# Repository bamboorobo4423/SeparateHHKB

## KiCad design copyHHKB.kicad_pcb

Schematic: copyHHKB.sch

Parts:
!1: SW_DIP_x01; MX_PCB_100H
$1: SW_DIP_x01; MX_PCB_100H
%1: SW_DIP_x01; MX_PCB_100H
&1: SW_DIP_x01; MX_PCB_100H
'1: SW_DIP_x01; MX_PCB_100H
(1: SW_DIP_x01; MX_PCB_100H
)1: SW_DIP_x01; MX_PCB_100H
*1: SW_DIP_x01; MX_PCB_100H
+1: SW_DIP_x01; MX_PCB_100H
/1: SW_DIP_x01; MX_PCB_100H
;1: SW_DIP_x01; MX_PCB_100H
<1: SW_DIP_x01; MX_PCB_100H
>1: SW_DIP_x01; MX_PCB_100H
@1: SW_DIP_x01; MX_PCB_100H
AltL1: SW_DIP_x01; Hybrid_Plate_125H
AltR1: SW_DIP_x01; Hybrid_Plate_125H
BackSP1: SW_DIP_x01; Hybrid_Plate_150H
Control1: SW_DIP_x01; Hybrid_Plate_175H
D1, D2, D3, D4, D5, D6, D7, D8, D9, D10, D11, D12, D13, D14, D15, D16, D17, D18, D19, D20, D21, D22, D23, D24, D25, D26, D27, D28, D29, D30, D31, D32, D33, D34, D35, D36, D37, D38, D39, D40, D41, D42, D43, D44, D45, D46, D47, D48, D49, D50, D51, D52, D53, D54, D55, D56, D57, D58, D59, D60: D; Diode-dual
D61: D; Diode
ESC1: SW_DIP_x01; Hybrid_PCB_100H
Enter1: SW_DIP_x01; Hybrid_PCB_225H
Fn1: SW_DIP_x01; Hybrid_PCB_100H
J1, J2: MJ-4PP-9; MJ-4PP-9_rev2
L1: SW_DIP_x01; Hybrid_PCB_100H
SP1: SW_DIP_x01; MX_PCB_275H
SP2: SW_DIP_x01; MX_Plate_225H
U1, U2: ProMicro
[1: SW_DIP_x01; MX_PCB_100H
]1: SW_DIP_x01; MX_PCB_100H
^1: SW_DIP_x01; MX_PCB_100H
_1: SW_DIP_x01; MX_PCB_100H
`1: SW_DIP_x01; MX_PCB_100H
a1: SW_DIP_x01; MX_PCB_100H
b1: SW_DIP_x01; MX_PCB_100H
c1: SW_DIP_x01; MX_PCB_100H
d1: SW_DIP_x01; MX_PCB_100H
e1: SW_DIP_x01; Hybrid_PCB_100H
f1: SW_DIP_x01; Hybrid_PCB_100H
g1: SW_DIP_x01; Hybrid_PCB_100H
h1: SW_DIP_x01; Hybrid_PCB_100H
i1: SW_DIP_x01; Hybrid_PCB_100H
j1: SW_DIP_x01; Hybrid_PCB_100H
k1: SW_DIP_x01; Hybrid_PCB_100H
m1: SW_DIP_x01; Hybrid_PCB_100H
n1: SW_DIP_x01; Hybrid_PCB_100H
o1: SW_DIP_x01; Hybrid_PCB_100H
p1: SW_DIP_x01; Hybrid_PCB_100H
p2, p3: 3pin; StripLED_rev
q1: SW_DIP_x01; Hybrid_PCB_100H
r1: SW_DIP_x01; Hybrid_PCB_100H
s1: SW_DIP_x01; Hybrid_PCB_100H
s2, s3: sw; TSHA-T-2.5B2-19E]
sharp1: SW_DIP_x01; MX_Plate_100H
shiftL1: SW_DIP_x01; Hybrid_Plate_225H
shiftR1: SW_DIP_x01; Hybrid_Plate_175H
t1: SW_DIP_x01; MX_Plate_100H
tab1: SW_DIP_x01; Hybrid_PCB_150H
u1: SW_DIP_x01; MX_Plate_100H
v1: SW_DIP_x01; MX_Plate_100H
w1: SW_DIP_x01; MX_Plate_100H
winL1: SW_DIP_x01; MX_Plate_100H
winR1: SW_DIP_x01; MX_Plate_100H
x1: SW_DIP_x01; MX_Plate_100H
y1: SW_DIP_x01; MX_Plate_100H
z1: SW_DIP_x01; MX_Plate_100H
|1: SW_DIP_x01; MX_Plate_100H

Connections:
LGND: J2.C, U2.3 (GND), U2.4 (GND), U2.23 (GND), p3.1 (GND), s3.1
LLED: U2.1 (TX), p3.2
LVCC: J2.D, U2.21 (VCC), p3.3 (VCC)
Lcol6: U2.20 (F4), ^1.1, h1.1, y1.1
Lcol7: &1.1, U2.19 (F5), j1.1, n1.1, u1.1
Lcol8: *1.1, SP2.1, U2.18 (F6), i1.1, k1.1, m1.1
Lcol9: (1.1, <1.1, L1.1, U2.17 (F7), `1.1, o1.1
Lcol10: )1.1, ;1.1, >1.1, U2.16 (B1), p1.1, winR1.1
Lcol11: '1.1, /1.1, AltR1.1, U2.15 (B3), [1.1, _1.1
Lcol12: +1.1, Fn1.1, U2.14 (B2), ]1.1
Lcol13: BackSP1.1, Enter1.1, U2.13 (B6), shiftR1.1, |1.1
Ldate: J2.B, U2.2 (RX)
Lrow0: D28.1 (K), D31.1 (K), D35.1 (K), D39.1 (K), D44.1 (K), D49.1 (K), D54.1 (K), D57.1 (K), U2.7 (D4)
Lrow1: D29.1 (K), D32.1 (K), D36.1 (K), D40.1 (K), D45.1 (K), D50.1 (K), D55.1 (K), D58.1 (K), U2.8 (C6)
Lrow2: D30.1 (K), D33.1 (K), D37.1 (K), D41.1 (K), D46.1 (K), D51.1 (K), D59.1 (K), U2.9 (D7)
Lrow3: D34.1 (K), D38.1 (K), D42.1 (K), D47.1 (K), D52.1 (K), D56.1 (K), D60.1 (K), U2.10 (E6)
Lrow4: D43.1 (K), D48.1 (K), D53.1 (K), D61.1 (K), U2.11 (B4)
unnamed: !1.2, D5.2 (A)
unnamed: $1.2, D18.2 (A)
unnamed: %1.2, D22.2 (A)
unnamed: &1.2, D31.2 (A)
unnamed: '1.2, D51.2 (A)
unnamed: (1.2, D39.2 (A)
unnamed: )1.2, D44.2 (A)
unnamed: *1.2, D35.2 (A)
unnamed: +1.2, D54.2 (A)
unnamed: /1.2, D52.2 (A)
unnamed: ;1.2, D46.2 (A)
unnamed: <1.2, D42.2 (A)
unnamed: >1.2, D47.2 (A)
unnamed: @1.2, D9.2 (A)
unnamed: AltL1.2, D8.2 (A)
unnamed: AltR1.2, D53.2 (A)
unnamed: BackSP1.2, D58.2 (A)
unnamed: Control1.2, D3.2 (A)
unnamed: D1.2 (A), ESC1.2
unnamed: D2.2 (A), tab1.2
unnamed: D4.2 (A), shiftL1.2
unnamed: D6.2 (A), q1.2
unnamed: D7.2 (A), a1.2
unnamed: D10.2 (A), w1.2
unnamed: D11.2 (A), s1.2
unnamed: D12.2 (A), z1.2
unnamed: D13.2 (A), winL1.2
unnamed: D14.2 (A), sharp1.2
unnamed: D15.2 (A), e1.2
unnamed: D16.2 (A), d1.2
unnamed: D17.2 (A), x1.2
unnamed: D19.2 (A), r1.2
unnamed: D20.2 (A), f1.2
unnamed: D21.2 (A), c1.2
unnamed: D23.2 (A), t1.2
unnamed: D24.2 (A), g1.2
unnamed: D25.2 (A), v1.2
unnamed: D26.2 (A), SP1.2
unnamed: D27.2 (A), b1.2
unnamed: D28.2 (A), ^1.2
unnamed: D29.2 (A), y1.2
unnamed: D30.2 (A), h1.2
unnamed: D32.2 (A), u1.2
unnamed: D33.2 (A), j1.2
unnamed: D34.2 (A), n1.2
unnamed: D36.2 (A), i1.2
unnamed: D37.2 (A), k1.2
unnamed: D38.2 (A), m1.2
unnamed: D40.2 (A), o1.2
unnamed: D41.2 (A), L1.2
unnamed: D43.2 (A), `1.2
unnamed: D45.2 (A), p1.2
unnamed: D48.2 (A), winR1.2
unnamed: D49.2 (A), _1.2
unnamed: D50.2 (A), [1.2
unnamed: D55.2 (A), ]1.2
unnamed: D56.2 (A), Fn1.2
unnamed: D57.2 (A), |1.2
unnamed: D59.2 (A), Enter1.2
unnamed: D60.2 (A), shiftR1.2
unnamed: D61.2 (A), SP2.2
unnamed: U1.22 (RST), s2.4
unnamed: U2.22 (RST), s3.4
RGND: J1.C, U1.3 (GND), U1.4 (GND), U1.23 (GND), p2.3 (VCC), s2.1
RLED: U1.1 (TX), p2.2
RVCC: J1.D, U1.21 (VCC), p2.1 (GND)
Rcol0: Control1.1, ESC1.1, U1.20 (F4), shiftL1.1, tab1.1
Rcol1: !1.1, AltL1.1, U1.19 (F5), a1.1, q1.1
Rcol2: @1.1, U1.18 (F6), s1.1, w1.1, winL1.1, z1.1
Rcol3: U1.17 (F7), d1.1, e1.1, sharp1.1, x1.1
Rcol4: $1.1, U1.16 (B1), c1.1, f1.1, r1.1
Rcol5: %1.1, SP1.1, U1.15 (B3), g1.1, t1.1, v1.1
Rcol6: U1.14 (B2), b1.1
Rdate: J1.B, U1.2 (RX)
Rrow0: D1.1 (K), D5.1 (K), D9.1 (K), D14.1 (K), D18.1 (K), D22.1 (K), U1.7 (D4)
Rrow1: D2.1 (K), D6.1 (K), D10.1 (K), D15.1 (K), D19.1 (K), D23.1 (K), U1.8 (C6)
Rrow2: D3.1 (K), D7.1 (K), D11.1 (K), D16.1 (K), D20.1 (K), D24.1 (K), U1.9 (D7)
Rrow3: D4.1 (K), D12.1 (K), D17.1 (K), D21.1 (K), D25.1 (K), D27.1 (K), U1.10 (E6)
Rrow4: D8.1 (K), D13.1 (K), D26.1 (K), U1.11 (B4)

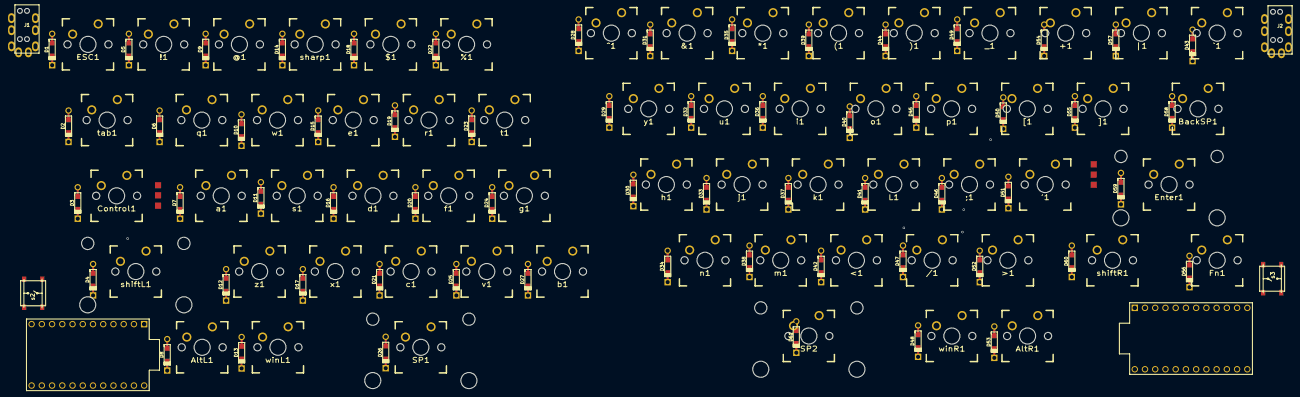
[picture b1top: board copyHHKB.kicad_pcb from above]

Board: 2 copper layers, 130 parts (1 on the bottom side), 96 nets, no tracks yet.

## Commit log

2018-08-16 とりあえずコピー
2018-08-16 作ってる
2018-08-16 とりあえず回路図はできたかな
2018-09-13 ちょっと前にスイッチの街がとかを修正したやつ
